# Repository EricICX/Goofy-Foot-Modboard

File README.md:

# Goofy Foot Modboard

A NES controller PCB design with support for Goofy Foot and normal bindings.

Initially created by me after I found out that my best controller PCB was one from a third party controller that used HASL for the contacts, rather than carbon ink like the originals.

Fun fact: this design has zero vias!

## What's Included

This repository includes [the necessary gerber files to fabricate this PCB yourself](https://github.com/EricICX/Goofy-Foot-Modboard/raw/main/gerbers-v1.1.zip), along with the necessary files to edit this design in KiCAD.

# Credits
Edge cuts from [AutumnHippo's NES64 project](https://gitlab.com/nes64/NES64)

Dimensions from [Elektronaut's DXF drawing](https://www.elektronaut.at/nes-gamepad-dimensions-pictures/624)

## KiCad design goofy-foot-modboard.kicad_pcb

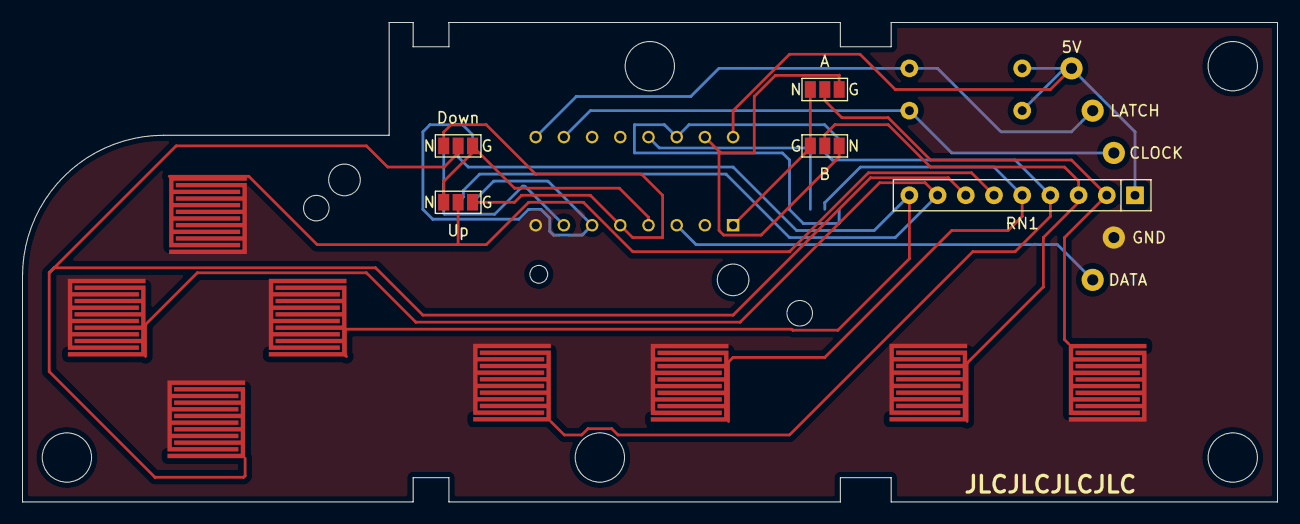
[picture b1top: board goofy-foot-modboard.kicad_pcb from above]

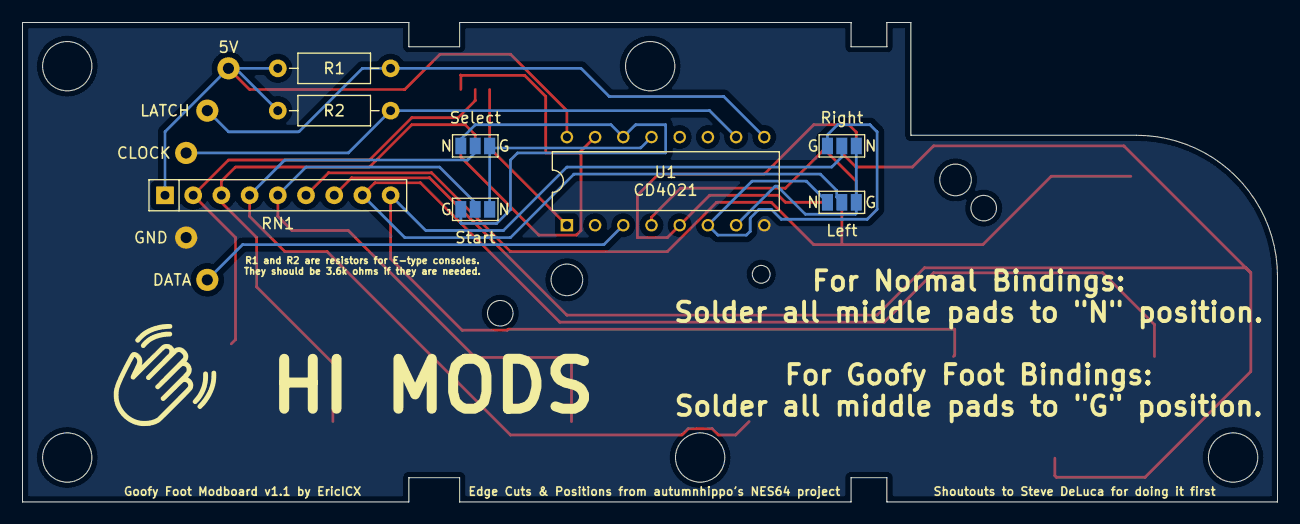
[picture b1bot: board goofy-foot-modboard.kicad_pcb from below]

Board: 2 copper layers, 113.0 x 43.2 mm, 35 parts (8 on the bottom side), 21 nets.

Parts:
@HOLE0, @HOLE1, @HOLE2, @HOLE3, @HOLE4, @HOLE5, @HOLE6, @HOLE7, @HOLE8, @HOLE9: (no value)
J1: NES_Latch; Controller_Cord_Pad
J2: NES_Clock; Controller_Cord_Pad
J3: NES_Data; Controller_Cord_Pad
J4: NES_5V; Controller_Cord_Pad
J5: NES_GND; Controller_Cord_Pad
JP1: Right_Jumper; SolderJumper-3_P1.3mm_Open_Pad1.0x1.5mm_NumberLabels
JP2: Left_Jumper; SolderJumper-3_P1.3mm_Open_Pad1.0x1.5mm_NumberLabels
JP4: Up_Jumper; SolderJumper-3_P1.3mm_Open_Pad1.0x1.5mm_NumberLabels
JP5: Start_Jumper; SolderJumper-3_P1.3mm_Open_Pad1.0x1.5mm_NumberLabels
JP6: Select_Jumper; SolderJumper-3_P1.3mm_Open_Pad1.0x1.5mm_NumberLabels
JP7: B_Jumper; SolderJumper-3_P1.3mm_Open_Pad1.0x1.5mm_NumberLabels
JP8: A_Jumper; SolderJumper-3_P1.3mm_Open_Pad1.0x1.5mm_NumberLabels
JPd: Down_Jumper; SolderJumper-3_P1.3mm_Open_Pad1.0x1.5mm_NumberLabels
R1, R2: 3.6k; R_Axial_DIN0207_L6.3mm_D2.5mm_P10.16mm_Horizontal
RN1: R_Network08; R_Array_SIP9
S1: Right_Pad; Controller-Pad
S2: Left_Pad; Controller-Pad
S3: Down_Pad; Controller-Pad
S4: Up_Pad; Controller-Pad
S5: Start_Button; Controller-Pad
S6: Select_Button; Controller-Pad
S7: B_Button; Controller-Pad
S8: A_Button; Controller-Pad
U1: CD4021; DIP794W53P254L1930H508Q16N

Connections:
+5V: J4.1, R1.1, R2.2, RN1.1 (common), U1.16 (VDD)
GND: J5.1, S1.1 (A), S2.1 (A), S3.1 (A), S4.1 (A), S5.1 (A), S6.1 (A), S7.1 (A), S8.1 (A), U1.8 (VSS)
unnamed: J1.1, R1.2, U1.9 (PL)
unnamed: J2.1, R2.1, U1.10 (CP)
unnamed: J3.1, U1.3 (Q7)
unnamed: JP4.1 (A), JPd.1 (A), U1.4 (D3)
unnamed: JP4.3 (B), JPd.3 (B), U1.5 (D2)
unnamed: JP5.3 (B), JP6.3 (B), U1.13 (D4)
unnamed: JP4.2 (C), RN1.6 (R5), S4.2 (B)
unnamed: JP1.2 (C), RN1.9 (R8), S1.2 (B)
unnamed: JP2.2 (C), RN1.8 (R7), S2.2 (B)
unnamed: JPd.2 (C), RN1.7 (R6), S3.2 (B)
unnamed: JP5.2 (C), RN1.5 (R4), S5.2 (B)
unnamed: JP6.2 (C), RN1.4 (R3), S6.2 (B)
unnamed: JP7.2 (C), RN1.3 (R2), S7.2 (B)
unnamed: JP8.2 (C), RN1.2 (R1), S8.2 (B)
unnamed: JP7.1 (A), JP8.1 (A), U1.1 (D7)
unnamed: JP1.1 (A), JP2.1 (A), U1.6 (D1)
unnamed: JP1.3 (B), JP2.3 (B), U1.7 (D0)
unnamed: JP5.1 (A), JP6.1 (A), U1.14 (D5)
unnamed: JP7.3 (B), JP8.3 (B), U1.15 (D6)

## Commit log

2022-11-21 Version 1.1
